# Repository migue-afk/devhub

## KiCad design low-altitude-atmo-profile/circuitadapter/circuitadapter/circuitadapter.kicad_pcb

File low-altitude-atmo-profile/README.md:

# Low-Altitude Atmospheric Profile

An embedded data acquisition system designed to collect **atmospheric and telemetry measurements during low-altitude flights**.

The project combines UAV telemetry with environmental sensors to record altitude and temperature data for later analysis.

## Overview

The system receives **LTM (Lightweight Telemetry)** data from a flight controller while simultaneously reading several environmental sensors.

Measurements are periodically stored on an SD card, allowing the creation of an atmospheric profile based on altitude.

The project currently integrates:

* LTM telemetry
* GPS altitude
* DS18B20 digital temperature sensor
* NTC thermistor
* DHT22 temperature and humidity sensor
* SD card data logging
* NeoPixel status indicators
* Serial debugging

## System Architecture

```text
                 ┌───────────────────┐
                 │ Flight Controller │
                 │   LTM Telemetry   │
                 └─────────┬─────────┘
                           │
                           ▼
                  ┌─────────────────┐
                  │ Microcontroller │
                  └────────┬────────┘
                           │
           ┌───────────────┼───────────────┐
           │               │               │
           ▼               ▼               ▼
       DS18B20            NTC            DHT22
     Temperature      Temperature    Temp / Humidity
           │               │               │
           └───────────────┼───────────────┘
                           │
                           ▼
                     Data Processing
                           │
                  ┌────────┴─────────┐
                  │                  │
                  ▼                  ▼
              SD Logging       NeoPixel Status
```

## Features

### LTM Telemetry

The firmware receives and processes LTM telemetry frames through a serial connection.

Currently extracted telemetry information includes:

* GPS altitude
* Satellite count
* Battery voltage
* Armed / disarmed state
* Flight mode

Altitude data can be combined directly with environmental measurements.

### Temperature Measurement

The project supports multiple temperature sensing methods.

#### DS18B20

A digital temperature sensor connected through the OneWire protocol.

The sensor is configured with 12-bit resolution and asynchronous temperature conversion.

#### NTC Thermistor

An analog NTC thermistor is used as an additional temperature source.

This provides an alternative measurement method that can be compared with the DS18B20 data.

#### DHT22

The project also contains support for a DHT22 sensor for:

* Temperature
* Relative humidity

DHT22 support is currently available in the codebase and can be enabled when required.

## Data Logging

Measurements are written periodically to an SD card.

The current logging system can store values such as:

```text
Elapsed Time
Altitude
DS18B20 Temperature
NTC Temperature
```

These measurements can later be processed to study temperature variation with altitude.

## Project Structure

```text
low-altitude-atmo-profile/
├── low-altitude-atmo-profile.ino
├── DHTsensor.cpp
├── DHTsensor.h
├── ds18b20.cpp
├── ds18b20.h
├── ntc.cpp
├── ntc.h
├── LTMtelemetry.cpp
├── LTMtelemetry.h
├── SDsave.cpp
├── SDsave.h
├── Efectos.cpp
├── Efectos.h
├── debug.py
└── circuitadapter/
```

## Main Components

| File                            | Description                             |
| ------------------------------- | --------------------------------------- |
| `low-altitude-atmo-profile.ino` | Main firmware and acquisition loop      |
| `LTMtelemetry.cpp/.h`           | LTM telemetry processing                |
| `ds18b20.cpp/.h`                | DS18B20 temperature sensor interface    |
| `ntc.cpp/.h`                    | NTC thermistor measurement              |
| `DHTsensor.cpp/.h`              | DHT22 temperature/humidity interface    |
| `SDsave.cpp/.h`                 | SD card initialization and data logging |
| `Efectos.cpp/.h`                | NeoPixel visual status effects          |
| `debug.py`                      | Development/debugging utility           |

## Dependencies

The project uses Arduino-compatible libraries including:

```text
SoftwareSerial
Adafruit_NeoPixel
DHT
OneWire
DallasTemperature
SD
```

Install the required libraries using the Arduino IDE Library Manager or your preferred Arduino-compatible development environment.

## Getting Started

Clone the repository:

```bash
git clone https://github.com/migue-afk/devhub.git
```

Enter the project directory:

```bash
cd devhub/low-altitude-atmo-profile
```

Open:

```text
low-altitude-atmo-profile.ino
```

with the Arduino IDE.

Install the required libraries, select the correct microcontroller and serial port, and upload the firmware.

## Current Pin Configuration

The main firmware currently defines several hardware connections directly in the source code.

Examples include:

```cpp
#define DHT22_PIN 2
const int SENSOR_PIN = 5;
```

LTM telemetry is received through `SoftwareSerial`.

Pin assignments may need to be changed depending on the microcontroller and hardware configuration being used.

## Sampling

Environmental measurements are currently processed approximately once per second:

```cpp
const unsigned long interval = 1000;
```

This interval can be modified depending on the desired atmospheric profile resolution.

## Intended Data Flow

```text
Sensors
   │
   ▼
Microcontroller
   │
   ├── Read LTM altitude
   ├── Read DS18B20
   ├── Read NTC
   ├── Read DHT22
   │
   ▼
Combine Measurements
   │
   ▼
SD Card
   │
   ▼
Post-processing / Analysis
```

## Applications

The project can be used as a starting point for experiments involving:

* Low-altitude atmospheric profiling
* UAV-based environmental measurements
* Temperature vs. altitude studies
* Embedded data acquisition
* Flight telemetry integration
* Sensor comparison and calibration
* Environmental data logging

## Future Improvements

* [ ] Add barometric pressure sensing
* [ ] Enable DHT22 measurements in the main acquisition loop
* [ ] Store GPS coordinates
* [ ] Improve CSV data formatting
* [ ] Add timestamps to datasets
* [ ] Add sensor calibration routines
* [ ] Add telemetry integrity validation
* [ ] Create Python post-processing tools
* [ ] Automatically generate temperature-vs-altitude plots
* [ ] Document complete wiring diagrams
* [ ] Document the circuit adapter hardware
* [ ] Add example flight datasets

## License

This project is part of the `devhub` repository and is released under the **MIT License**.

See the repository's [LICENSE](../LICENSE) file for details.

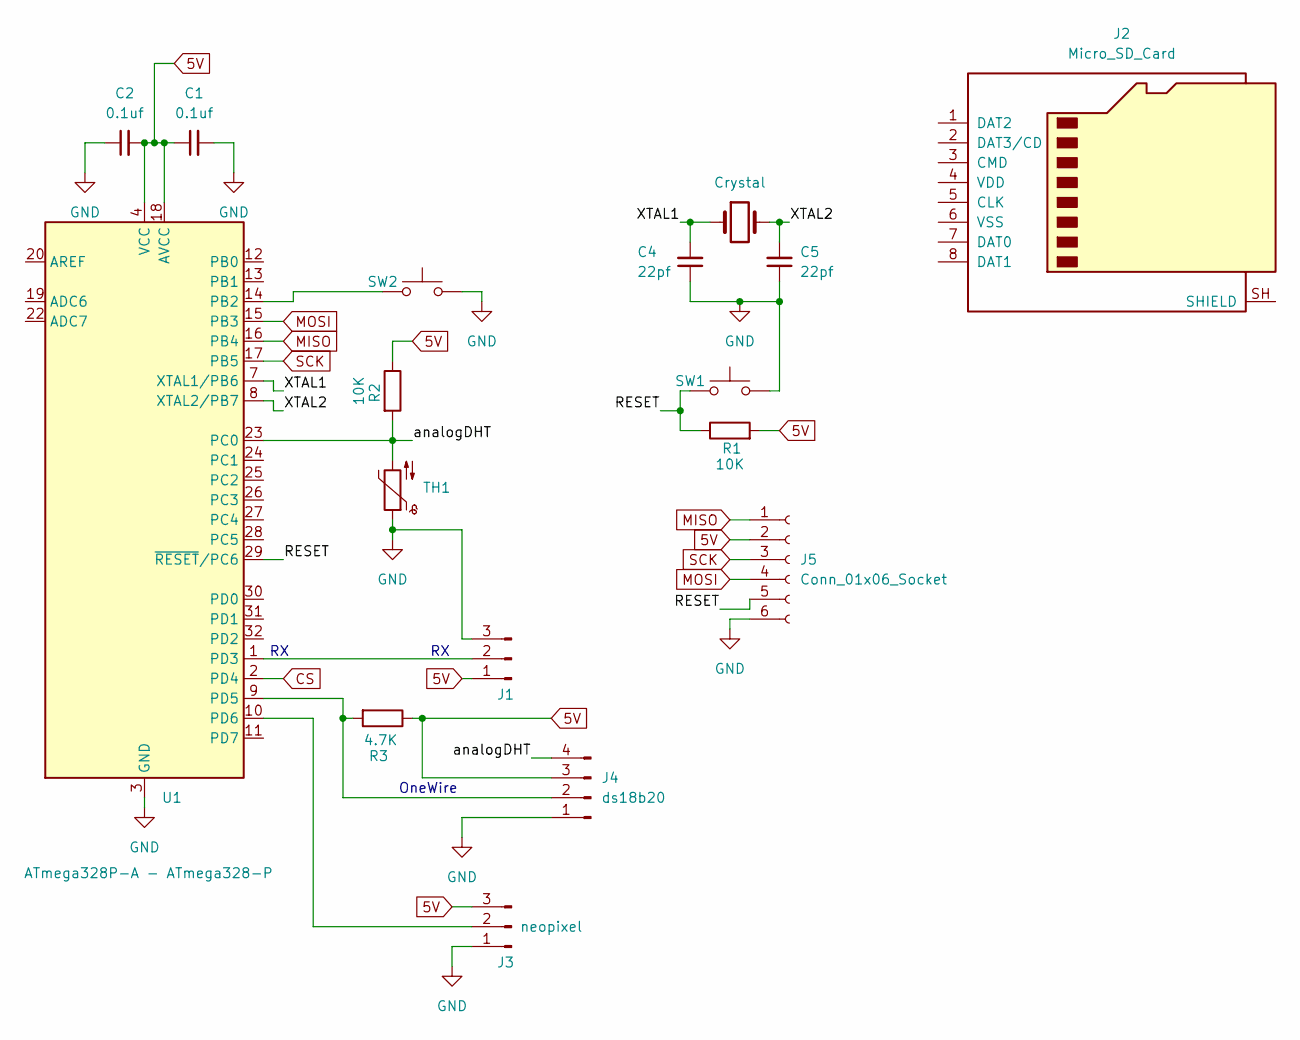
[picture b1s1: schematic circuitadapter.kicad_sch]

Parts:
C1, C2: 0.1uf; C_0504_1310Metric_Pad0.83x1.28mm_HandSolder
C4, C5: 22pf; C_0504_1310Metric_Pad0.83x1.28mm_HandSolder
J1: Conn_01x03_Pin; JST_SH_SM03B-SRSS-TB_1x03-1MP_P1.00mm_Horizontal
J2: Micro_SD_Card; microSD_HC_Hirose_DM3D-SF
J3: neopixel; JST_SH_SM03B-SRSS-TB_1x03-1MP_P1.00mm_Horizontal
J4: ds18b20; JST_SH_SM04B-SRSS-TB_1x04-1MP_P1.00mm_Horizontal
J5: Conn_01x06_Socket; PinHeader_2x03_P2.54mm_Horizontal
R1, R2: 10K; R_0508_1220Metric_Pad1.12x2.15mm_HandSolder
R3: 4.7K; R_0508_1220Metric_Pad1.12x2.15mm_HandSolder
SW1, SW2: SW_Push; SW_Push_SPST_NO_Alps_SKRK
TH1: 100K; R_0508_1220Metric_Pad1.12x2.15mm_HandSolder
U1: ATmega328P-A - ATmega328-P; TQFP-32_7x7mm_P0.8mm
Y1: Crystal; Crystal_SMD_3215-2Pin_3.2x1.5mm

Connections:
5V: C1.1, C2.2, J1.1, J3.3, J4.3, J5.2, R1.2, R2.1, R3.1, U1.4 (VCC), U1.6 (VCC), U1.18 (AVCC)
/RESET: J5.5, R1.1, SW1.1, U1.29 (~RESET/PC6)
/XTAL1: C4.2, U1.7 (XTAL1/PB6), Y1.1
/XTAL2: C5.2, U1.8 (XTAL2/PB7), Y1.2
/analogDHT: J4.4, R2.2, TH1.2, U1.23 (PC0)
CS: U1.2 (PD4)
GND: C1.2, C2.1, C4.1, C5.1, J1.3, J3.1, J4.1, J5.6, SW1.2, SW2.2, TH1.1, U1.3 (GND), U1.5 (GND), U1.21 (GND)
MISO: J5.1, U1.16 (PB4)
MOSI: J5.4, U1.15 (PB3)
unnamed: J1.2, U1.1 (PD3)
unnamed: J3.2, U1.10 (PD6)
unnamed: J4.2, R3.2, U1.9 (PD5)
unnamed: SW2.1, U1.14 (PB2)
SCK: J5.3, U1.17 (PB5)

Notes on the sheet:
OneWire

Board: 2 copper layers, 17 parts (1 on the bottom side), 13 nets, no tracks yet.

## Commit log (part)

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2026-03-18 added LTM efects for VLOS
2026-06-04 low altitude atmo profile - prototype
